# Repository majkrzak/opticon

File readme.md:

ὀπτικός
=======

Introduction
------------

Aim of the project is to explore USB protocol and create simple UVC device using Atmega32U4 builtin stack.

Hardware
--------

### 8x6 arduino shield

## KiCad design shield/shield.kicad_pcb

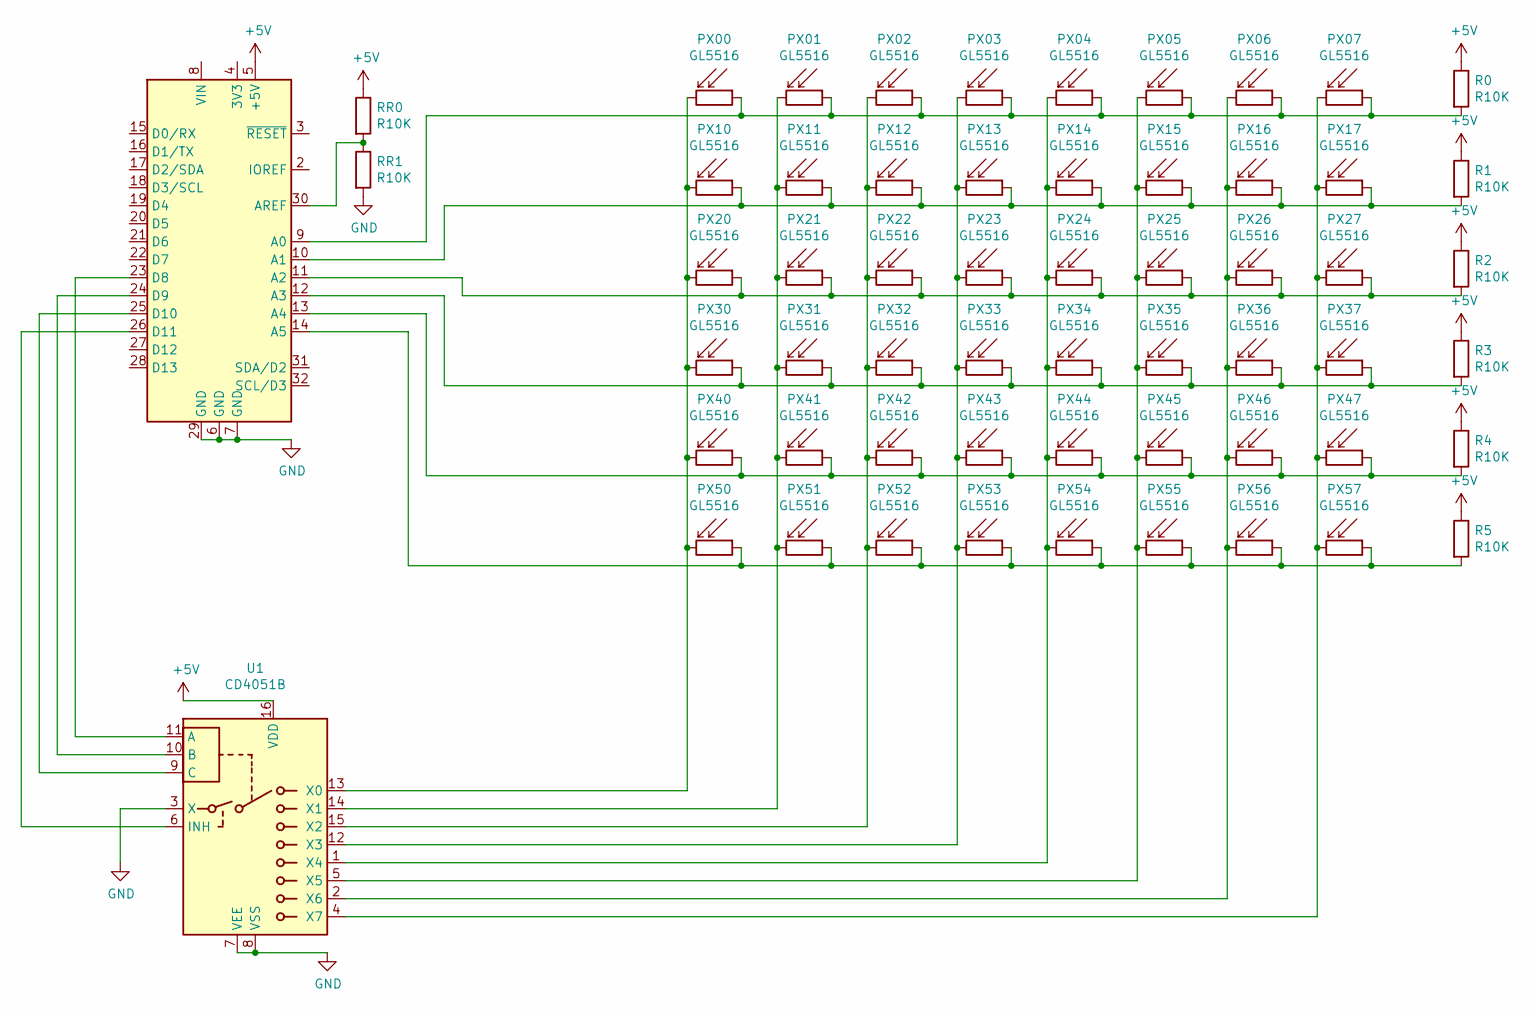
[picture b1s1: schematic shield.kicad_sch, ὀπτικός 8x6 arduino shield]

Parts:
A1: Arduino_Leonardo; Arduino_UNO_R3_WithMountingHoles
PX00, PX01, PX02, PX03, PX04, PX05, PX06, PX07, PX10, PX11, PX12, PX13, PX14, PX15, PX16, PX17, PX20, PX21, PX22, PX23, PX24, PX25, PX26, PX27, PX30, PX31, PX32, PX33, PX34, PX35, PX36, PX37, PX40, PX41, PX42, PX43, PX44, PX45, PX46, PX47, PX50, PX51, PX52, PX53, PX54, PX55, PX56, PX57: GL5516; R_LDR_5.1x4.3mm_P3.4mm_Vertical
R0, R1, R2, R3, R4, R5: R10K; R_Axial_DIN0207_L6.3mm_D2.5mm_P2.54mm_Vertical
RR0, RR1: R10K; R_Axial_DIN0207_L6.3mm_D2.5mm_P2.54mm_Vertical
U1: CD4051B; DIP-16_W7.62mm

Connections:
+5V: A1.5 (+5V), R0.1, R1.1, R2.1, R3.1, R4.1, R5.1, RR0.1, U1.16 (VDD)
GND: A1.6 (GND), A1.7 (GND), A1.29 (GND), RR1.2, U1.3 (X), U1.7 (VEE), U1.8 (VSS)
unnamed: A1.9 (A0), PX00.1, PX01.1, PX02.1, PX03.1, PX04.1, PX05.1, PX06.1, PX07.1, R0.2
unnamed: A1.10 (A1), PX10.1, PX11.1, PX12.1, PX13.1, PX14.1, PX15.1, PX16.1, PX17.1, R1.2
unnamed: A1.11 (A2), PX20.1, PX21.1, PX22.1, PX23.1, PX24.1, PX25.1, PX26.1, PX27.1, R2.2
unnamed: A1.12 (A3), PX30.1, PX31.1, PX32.1, PX33.1, PX34.1, PX35.1, PX36.1, PX37.1, R3.2
unnamed: A1.13 (A4), PX40.1, PX41.1, PX42.1, PX43.1, PX44.1, PX45.1, PX46.1, PX47.1, R4.2
unnamed: A1.14 (A5), PX50.1, PX51.1, PX52.1, PX53.1, PX54.1, PX55.1, PX56.1, PX57.1, R5.2
unnamed: A1.23 (D8), U1.11 (A)
unnamed: A1.24 (D9), U1.10 (B)
unnamed: A1.25 (D10), U1.9 (C)
unnamed: A1.26 (D11), U1.6 (INH)
unnamed: A1.30 (AREF), RR0.2, RR1.1
unnamed: PX00.2, PX10.2, PX20.2, PX30.2, PX40.2, PX50.2, U1.13 (X0)
unnamed: PX01.2, PX11.2, PX21.2, PX31.2, PX41.2, PX51.2, U1.14 (X1)
unnamed: PX02.2, PX12.2, PX22.2, PX32.2, PX42.2, PX52.2, U1.15 (X2)
unnamed: PX03.2, PX13.2, PX23.2, PX33.2, PX43.2, PX53.2, U1.12 (X3)
unnamed: PX04.2, PX14.2, PX24.2, PX34.2, PX44.2, PX54.2, U1.1 (X4)
unnamed: PX05.2, PX15.2, PX25.2, PX35.2, PX45.2, PX55.2, U1.5 (X5)
unnamed: PX06.2, PX16.2, PX26.2, PX36.2, PX46.2, PX56.2, U1.2 (X6)
unnamed: PX07.2, PX17.2, PX27.2, PX37.2, PX47.2, PX57.2, U1.4 (X7)

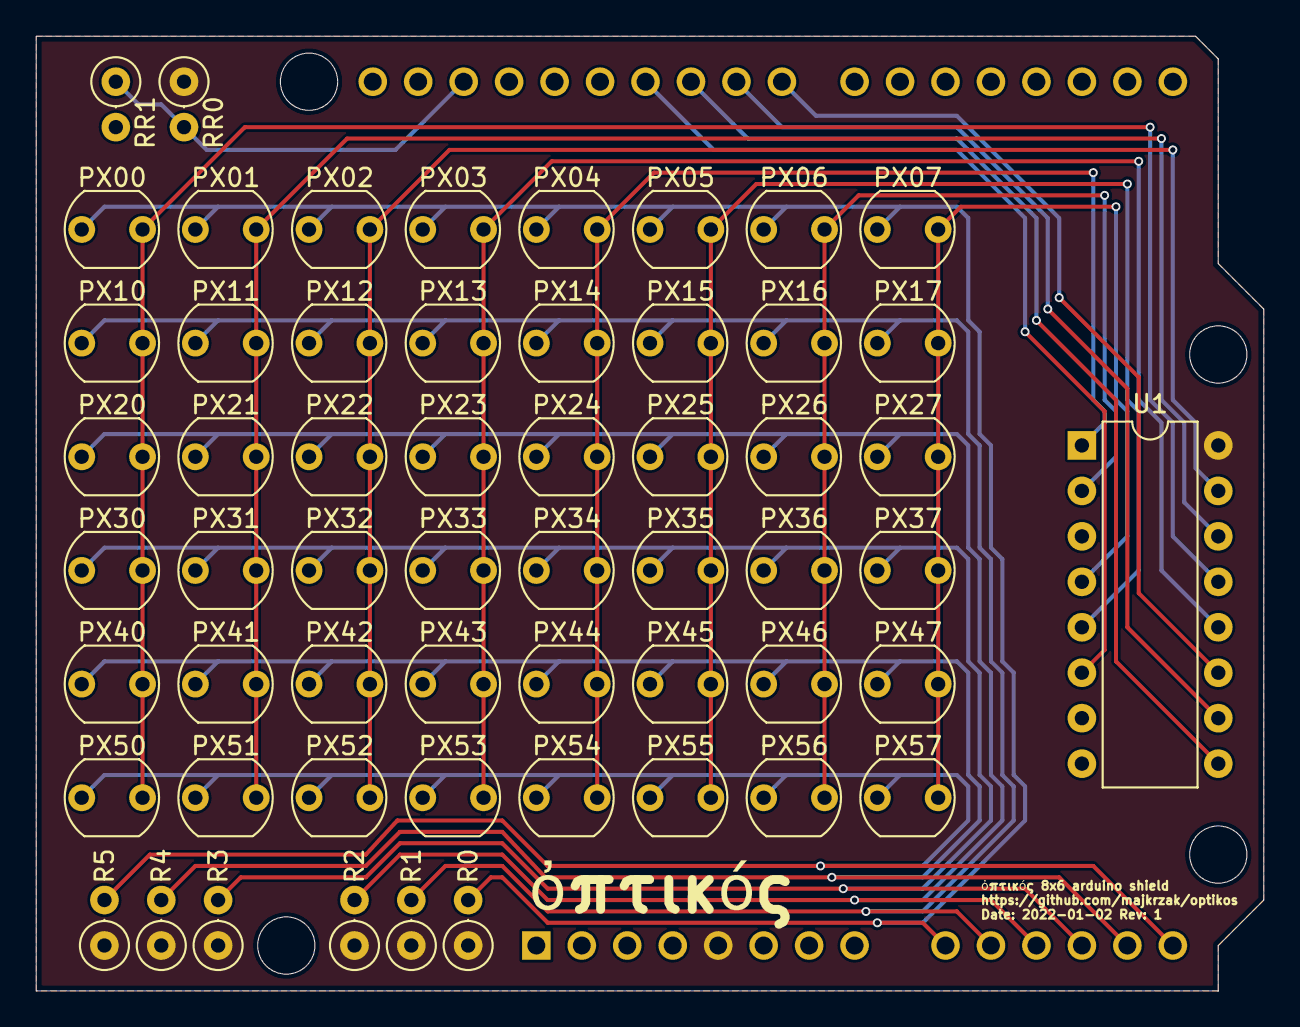
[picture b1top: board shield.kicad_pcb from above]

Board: 2 copper layers, 68.6 x 53.3 mm, 58 parts (1 on the bottom side), 21 nets.

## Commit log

2021-12-01 Add readme draft
2021-12-08 Add firmware skeleton and base usb setup.
    This mess is currently capable of registering USB device. Overal code structure is not yet established and will be for sure changed. Descriptors are going to be moved to the eprom and reading process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
2021-12-09 Add UVC 1.5 definitions
2021-12-09 Add some of video descriptors
2021-12-09 Add probably all video controll descriptors
2021-12-09 Add rest of descriptors
2021-12-09 Build descriptors bundle
2021-12-10 Add dummpy probe handshake
2021-12-16 Add control read
2021-12-16 Add status dummy handlers
2021-12-30 Send dummy frames
2022-01-01 Add arduino shield
2022-01-02 Update via spacing
2022-01-02 Update shield to kicad 6
2022-01-02 Update design rules
2022-01-02 Fix ground and vcc planes
2022-01-02 Release 8x6 arduino shield rev 1
2022-01-02 Add shield visualization to the readme
2022-01-04 Add simple ADC implementation
2022-01-04 Add image line reading
2022-01-05 Set framwe timing
2022-01-05 Add timer implementation
2022-01-06 Use scanning state machine
2022-01-23 Add mux driver
